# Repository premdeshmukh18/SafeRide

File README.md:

# SafeRide
By utilizing technology to identify potential safety hazards, the innovative project Saferide seeks to increase rider safety. Saferide promotes safe riding practices and reduces the risk of accidents and injuries by monitoring if a rider is wearing a helmet and is under the influence of alcohol. With more vehicles on the road and increased accidents and fatalities, there is a growing need for solutions promoting safe transportation practices. Saferide meets this need by employing sensors to detect possible safety hazards and inform riders and drivers when needed. Saferide has the ability to drastically minimize the risks connected with riding and make the roads safer.
## Table of Contents

- [Objectives](#objectives)
- [Block Diagram of the system](#blockdiagram)
- [Hardware Used](#hardware)
- [Software Requirements](#software)
- [Conclusion](#conclusion)
- [Future Scope](#futurescope)

## Objectives

  - To study statistics and research papers on existing projects related to the smart helmet to realize the depth of a problem and to define a final problem statement.
  - To Explore various electronic components and sensors applicable to the proposed system. Decide the most feasible components and check their availability in the market. Getting familiar with the Arduino IDE and design logic for integrating the microcontroller and various sensors.
  - To design a circuit diagram and use available simulation software to check the reliability of the designed circuit diagram.
  - To test and debug the finalized circuit diagram for various cases.

## BlockDiagram 

1. **Helmet Wear Check** block uses a push button to detect whether the rider is
wearing a helmet or not. The signal is interpreted by the ESP (microcontroller)
according to the logic of the code.
2. **Alcohol Detection** block utilizes an MQ3 sensor to detect alcohol levels. It
sends digital or analog signals within a certain range to indicate the presence
of alcohol.
3. The **Server** block, powered by an **ESP8266**, acts as a server. It collects data
from other blocks, checks if the rider is under the influence of alcohol,
Wearing a helmet verifies the receiver's presence on the other end. It
can communicate with the receiver using libraries like **ESPNOW** ([espnow library](https://github.com/yoursunny/WifiEspNow.git)) without
sending data to the cloud.
4. The **Receiver** block receives data from the server and enables other blocks
(such as I2C LCD and Motor) to function based on the received message.
5. The **I2C (LCD)** block uses the I2C protocol to interface with an LCD
display. It displays appropriate messages and warnings to the rider based on
the system's purpose.
6. The **Engine Motor** block represents a prototype of the actual motor on an electric
motorcycle. It consists of an L293D motor driver and a 5V DC toy motor.

### Hardware

● Push Button

● Alcohol Sensor MQ3 [4753]

● ESP8266 (NodeMCU)

● 16x2 (1602) Character Green Backlight LCD Display

● L293D Motor Driver

● 150 RPM Single Shaft DC Motor

### Software

[Arduino IDE(2.1.0)](https://docs.arduino.cc/software/ide-v2) and [ESP8266 library](https://github.com/esp8266/Arduino.git)

## Conclusion

The “SafeRide” project is a significant contribution to enhancing the safety of
motorcycle riders. The project involves the integration of different technologies to
develop a helmet that can detect Alcohol and helmet wear to improve safety. The
system includes sensors, microcontrollers, and wireless communication technologies.
The project aims to prevent accidents and reduce the severity of injuries in case of an
accident.

## FutureScope 

● Using FSR(Force sensitive resistor) instead of push-button for greater
accuracy and sensitivity.

● Improved data analysis: The data collected by the smart helmet system can be
analyzed to provide insights into the causes of accidents and help improve
safety policies and regulations.

● Integration with smart cities: The smart helmet system can be integrated with
smart city systems to provide real-time information on road conditions, traffic,
and weather conditions to enhance safety.

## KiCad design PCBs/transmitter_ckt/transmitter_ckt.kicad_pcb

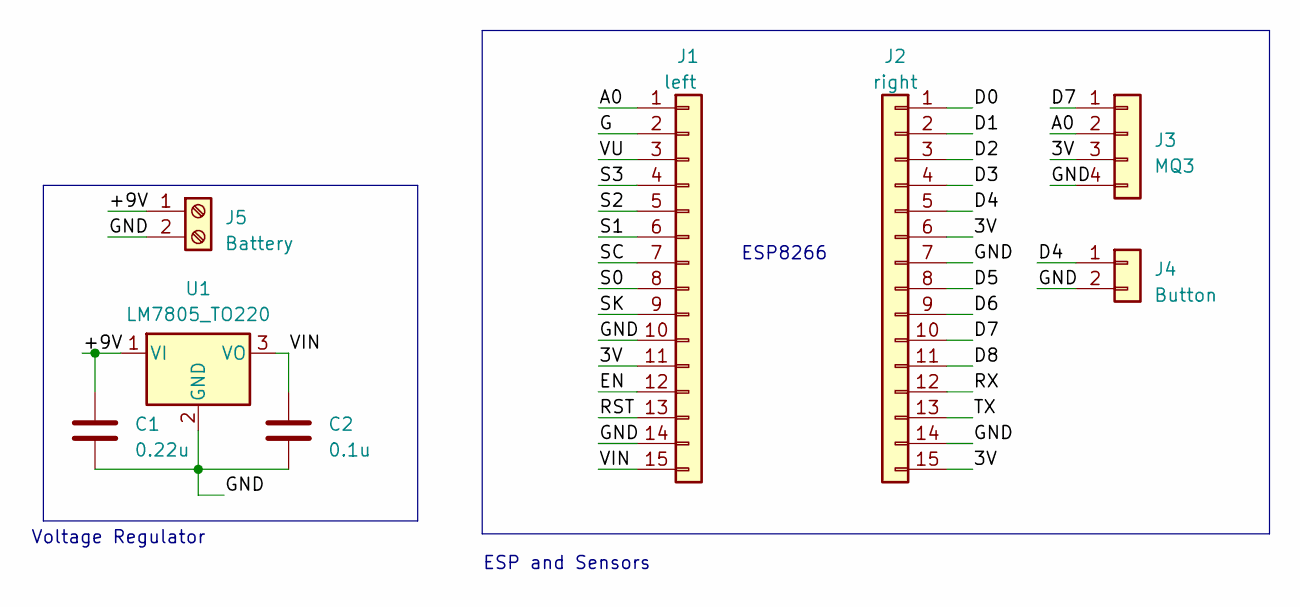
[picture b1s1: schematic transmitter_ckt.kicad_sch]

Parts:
C1: 0.22u
C2: 0.1u
J1: left; JST_EH_B15B-EH-A_1x15_P2.50mm_Vertical
J2: right
J3: MQ3
J4: Button
J5: Battery; TerminalBlock_Altech_AK300-2_P5.00mm
U1: LM7805_TO220; TO-220-3_Vertical

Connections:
/3V: J1.11, J2.6, J2.15, J3.3
/+9V: C1.1, J5.1, U1.1 (VI)
/A0: J1.1, J3.2
/D0: J2.1
/D1: J2.2
/D2: J2.3
/D3: J2.4
/D4: J2.5, J4.1
/D5: J2.8
/D6: J2.9
/D7: J2.10, J3.1
/D8: J2.11
/EN: J1.12
/G: J1.2
/GND: C1.2, C2.2, J1.10, J1.14, J2.7, J2.14, J3.4, J4.2, J5.2, U1.2 (GND)
/RST: J1.13
/RX: J2.12
/S0: J1.8
/S1: J1.6
/S2: J1.5
/S3: J1.4
/SC: J1.7
/SK: J1.9
/TX: J2.13
/VIN: C2.1, J1.15, U1.3 (VO)
/VU: J1.3

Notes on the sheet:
ESP8266
Voltage Regulator
ESP and Sensors

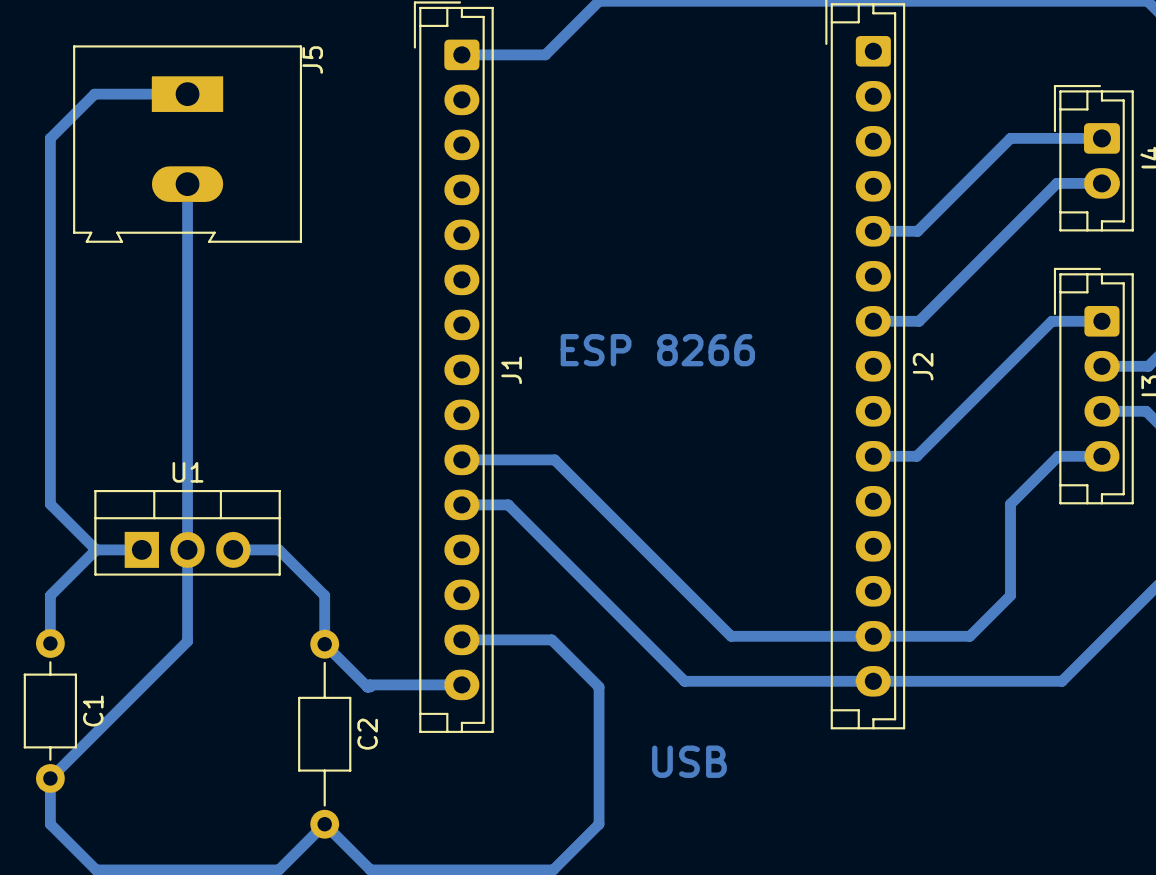
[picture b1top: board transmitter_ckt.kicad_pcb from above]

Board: 2 copper layers, 8 parts (0 on the bottom side), 7 nets.

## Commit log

2023-03-23 documentation of saferide smart helmet
2023-05-08 Uploaded test codes and final Project code
2023-05-11 esp8266 Controller ckt PCB upload
2023-05-11 Removed Files that were not required
2023-05-17 Reciever Schematic Uploaded
